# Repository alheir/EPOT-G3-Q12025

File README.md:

# Power Electronics (EPOT) - ITBA
**2025 Q1 - Group 3**

## Members
- Cílfone
- Di Sanzo
- Figueroa
- Gioia
- Heir

## Repository Contents
This repository contains the assignments (TPs) developed for the course 22.14 - Power Electronics of the Electronic Engineering career at ITBA (Instituto Tecnológico de Buenos Aires).

### [TP1: Boost Converter](./tps/tp1/README.md)
Design and simulation of a step-up converter (Boost).

### [TP2: Flyback Converter](./tps/tp2/README.md)
Design and simulation of a Flyback converter, including PCB design.

### [TP3: Inverter](./tps/tp3/README.md)
Implementation of a DC-AC inverter with SPWM generation using ESP32.

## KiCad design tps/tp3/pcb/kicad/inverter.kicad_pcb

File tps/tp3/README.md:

# TP3: Inverter (DC-AC Inverter)

## Description
This assignment consists of implementing a **DC-AC Inverter** using the **SPWM** (Sinusoidal PWM) modulation technique. Signal generation is performed using an **ESP32** microcontroller.

## Features
- **SPWM Generation**: Implemented in firmware for the ESP32.
- **Frequency Control**:
    - **ADC Mode**: Controlled via potentiometer (Pin 34).
    - **Serial Mode**: Commands via terminal to set a specific frequency.
- **Frequency Range**: 15 Hz to 99 Hz.

## Project Structure
- `fw/`: Firmware source code (PlatformIO).
- `pcb/`: Power and control board design.
- `sim/`: Simulations of the power stage and filters.
- `measurements/`: Experimental measurements.
- `assignment/`: Assignment requirements.

## Serial Commands (in `fw`)
- `help`: Shows the command list.
- `mode adc`: Switches to potentiometer control mode.
- `mode serial`: Switches to command control mode.
- `freq <value>`: Sets the frequency (only in serial mode).
- `start`/`stop`: Starts or stops PWM generation.

## PCB Renders
3D Renders of the Inverter control and power board:

> *3D Render - Perspective*:

> *3D Render - Top View*:

> *3D Render - Bottom View*:

## Authors
- G3: Cílfone, Di Sanzo, Figueroa, Gioia, Heir

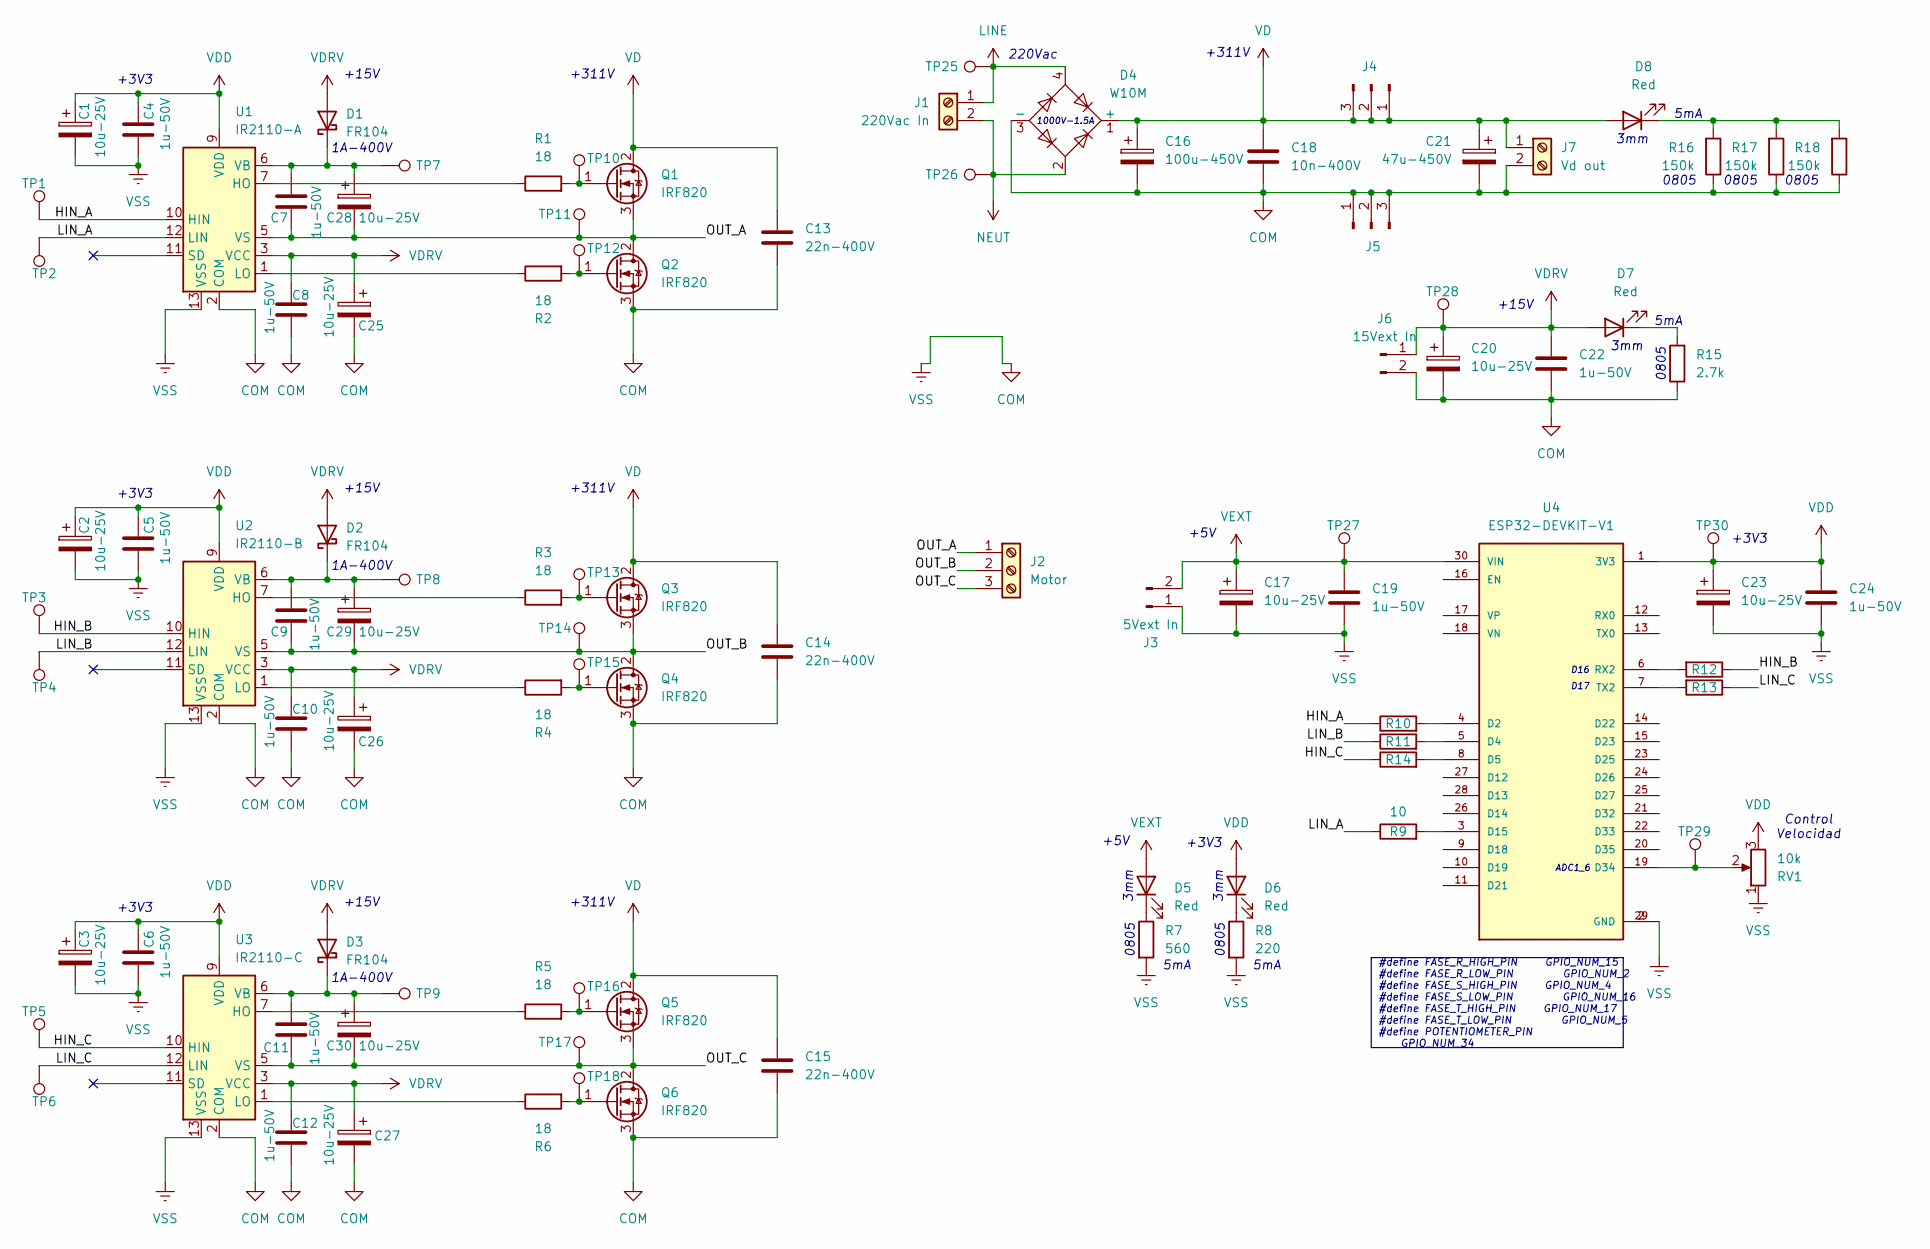
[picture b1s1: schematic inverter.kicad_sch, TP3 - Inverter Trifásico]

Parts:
C1, C2, C3, C17, C20, C23, C25, C26, C27, C28, C29, C30: 10u-25V; CP_Radial_D4.0mm_P1.50mm
C4, C5, C6, C7, C8, C9, C10, C11, C12, C19, C22, C24: 1u-50V; C_Disc_D4.7mm_W2.5mm_P5.00mm
C13, C14, C15: 22n-400V; C_Rect_L11.5mm_W4.0mm_P10.00mm_MKT
C16: 100u-450V; CP_Radial_D17.0mm_P7.50mm
C18: 10n-400V; C_Rect_L11.5mm_W4.5mm_P10.00mm_MKT
C21: 47u-450V; CP_Radial_D16.0mm_P7.50mm
D1, D2, D3: FR104; D_DO-41_SOD81_P10.16mm_Horizontal
D4: W10M; Diode_Bridge_Round_D9.0mm
D5, D6, D7, D8: Red; LED_D3.0mm
J1: 220Vac In; TerminalBlock_bornier-2_P5.08mm
J2: Motor; TerminalBlock_bornier-3_P5.08mm
J3: 5Vext In; Molex_KK-254_AE-6410-02A_1x02_P2.54mm_Vertical
J4, J5: Conn_01x03_Pin; PinHeader_1x03_P2.54mm_Vertical
J6: 15Vext In; Molex_KK-254_AE-6410-02A_1x02_P2.54mm_Vertical
J7: Vd out; TerminalBlock_bornier-2_P5.08mm
Q1, Q2, Q3, Q4, Q5, Q6: IRF820; TO-220-3_Vertical
R1, R2, R3, R4, R5, R6: 18; R_Axial_DIN0204_L3.6mm_D1.6mm_P7.62mm_Horizontal
R7: 560; R_0805_2012Metric_Pad1.20x1.40mm_HandSolder
R8: 220; R_0805_2012Metric_Pad1.20x1.40mm_HandSolder
R9, R10, R11, R12, R13, R14: 10; R_Axial_DIN0207_L6.3mm_D2.5mm_P10.16mm_Horizontal
R15: 2.7k; R_0805_2012Metric_Pad1.20x1.40mm_HandSolder
R16, R17, R18: 150k; R_0805_2012Metric_Pad1.20x1.40mm_HandSolder
RV1: 10k; Potentiometer_Alps_RK163_Single_Horizontal
TP1, TP2, TP3, TP4, TP5, TP6, TP7, TP8, TP9, TP10, TP11, TP12, TP13, TP14, TP15, TP16, TP17, TP18, TP25, TP26, TP27, TP28, TP29, TP30: TestPoint; PinHeader_1x01_P2.54mm_Vertical
U1: IR2110-A; DIP-14_W7.62mm_Socket_LongPads
U2: IR2110-B; DIP-14_W7.62mm_Socket_LongPads
U3: IR2110-C; DIP-14_W7.62mm_Socket_LongPads
U4: ESP32-DEVKIT-V1; MODULE_ESP32_DEVKIT_V1; PARTREV N/A

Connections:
/HIN_A: R10.1, TP1.1, U1.10 (HIN)
/HIN_B: R12.1, TP3.1, U2.10 (HIN)
/HIN_C: R14.1, TP5.1, U3.10 (HIN)
/LIN_A: R9.1, TP2.1, U1.12 (LIN)
/LIN_B: R11.1, TP4.1, U2.12 (LIN)
/LIN_C: R13.1, TP6.1, U3.12 (LIN)
/OUT_A: C7.2, C28.2, J2.1, Q1.3 (S), Q2.2 (D), TP11.1, U1.5 (VS)
/OUT_B: C9.2, C29.2, J2.2, Q3.3 (S), Q4.2 (D), TP14.1, U2.5 (VS)
/OUT_C: C11.2, C30.2, J2.3, Q5.3 (S), Q6.2 (D), TP17.1, U3.5 (VS)
COM: C1.2, C2.2, C3.2, C4.2, C5.2, C6.2, C8.2, C10.2, C12.2, C13.2, C14.2, C15.2, C16.2, C17.2, C18.2, C19.2, C20.2, C21.2, C22.2, C23.2, C24.2, C25.2, C26.2, C27.2, D4.3 (-), J3.1, J5.1, J5.2, J5.3, J6.2, J7.2, Q2.3 (S), Q4.3 (S), Q6.3 (S), R7.2, R8.2, R15.1, R16.1, R17.1, R18.1, RV1.1, U1.2 (COM), U1.13 (VSS), U2.2 (COM), U2.13 (VSS), U3.2 (COM), U3.13 (VSS), U4.2 (GND), U4.29 (GND)
LINE: D4.4, J1.1, TP25.1
NEUT: D4.2, J1.2, TP26.1
unnamed: C7.1, C28.1, D1.1 (K), TP7.1, U1.6 (VB)
unnamed: C9.1, C29.1, D2.1 (K), TP8.1, U2.6 (VB)
unnamed: C11.1, C30.1, D3.1 (K), TP9.1, U3.6 (VB)
unnamed: D5.1 (K), R7.1
unnamed: D6.1 (K), R8.1
unnamed: D7.1 (K), R15.2
unnamed: D8.1 (K), R16.2, R17.2, R18.2
unnamed: Q1.1 (G), R1.2, TP10.1
unnamed: Q2.1 (G), R2.2, TP12.1
unnamed: Q3.1 (G), R3.2, TP13.1
unnamed: Q4.1 (G), R4.2, TP15.1
unnamed: Q5.1 (G), R5.2, TP16.1
unnamed: Q6.1 (G), R6.2, TP18.1
unnamed: R1.1, U1.7 (HO)
unnamed: R2.1, U1.1 (LO)
unnamed: R3.1, U2.7 (HO)
unnamed: R4.1, U2.1 (LO)
unnamed: R5.1, U3.7 (HO)
unnamed: R6.1, U3.1 (LO)
unnamed: R10.2, U4.4 (D2)
unnamed: R11.2, U4.5 (D4)
unnamed: R14.2, U4.8 (D5)
unnamed: R9.2, U4.3 (D15)
unnamed: RV1.2, TP29.1, U4.19 (D34)
unnamed: R12.2, U4.6 (RX2)
unnamed: R13.2, U4.7 (TX2)
VD: C13.1, C14.1, C15.1, C16.1, C18.1, C21.1, D4.1 (+), D8.2 (A), J4.1, J4.2, J4.3, J7.1, Q1.2 (D), Q3.2 (D), Q5.2 (D)
VDD: C1.1, C2.1, C3.1, C4.1, C5.1, C6.1, C23.1, C24.1, D6.2 (A), RV1.3, TP30.1, U1.9 (VDD), U2.9 (VDD), U3.9 (VDD), U4.1 (3V3)
VDRV: C8.1, C10.1, C12.1, C20.1, C22.1, C25.1, C26.1, C27.1, D1.2 (A), D2.2 (A), D3.2 (A), D7.2 (A), J6.1, TP28.1, U1.3 (VCC), U2.3 (VCC), U3.3 (VCC)
VEXT: C17.1, C19.1, D5.2 (A), J3.2, TP27.1, U4.30 (VIN)

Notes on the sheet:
0805
5mA
+3V3
Control Velocidad
3mm
+311V
+15V
+5V
1A-400V
220Vac
D17
1000V-1.5A
ADC1_6
D16
#define FASE_R_HIGH_PIN GPIO_NUM_15 #define FASE_R_LOW_PIN GPIO_NUM_2 #define FASE_S_HIGH_PIN GPIO_NUM_4 #define FASE_S_LOW_PIN GPIO_NUM_16 #define FASE_T_HIGH_PIN GPIO_NUM_17 #define FASE_T_LOW_PIN GPIO_NUM_5 #define POTENTIOMETER_PIN GPIO_NUM_34

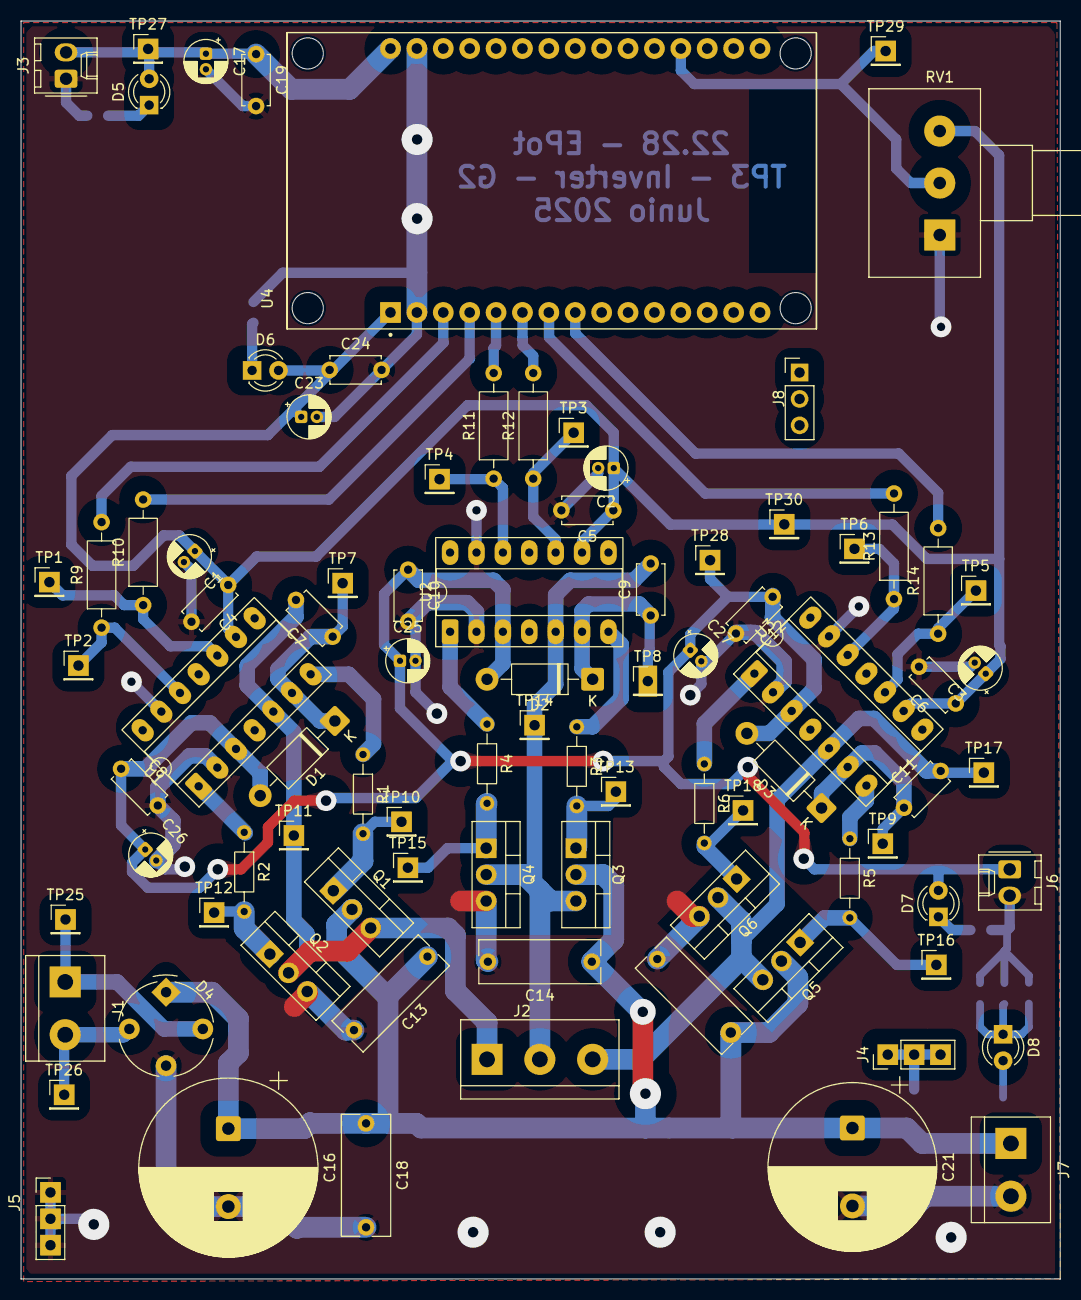
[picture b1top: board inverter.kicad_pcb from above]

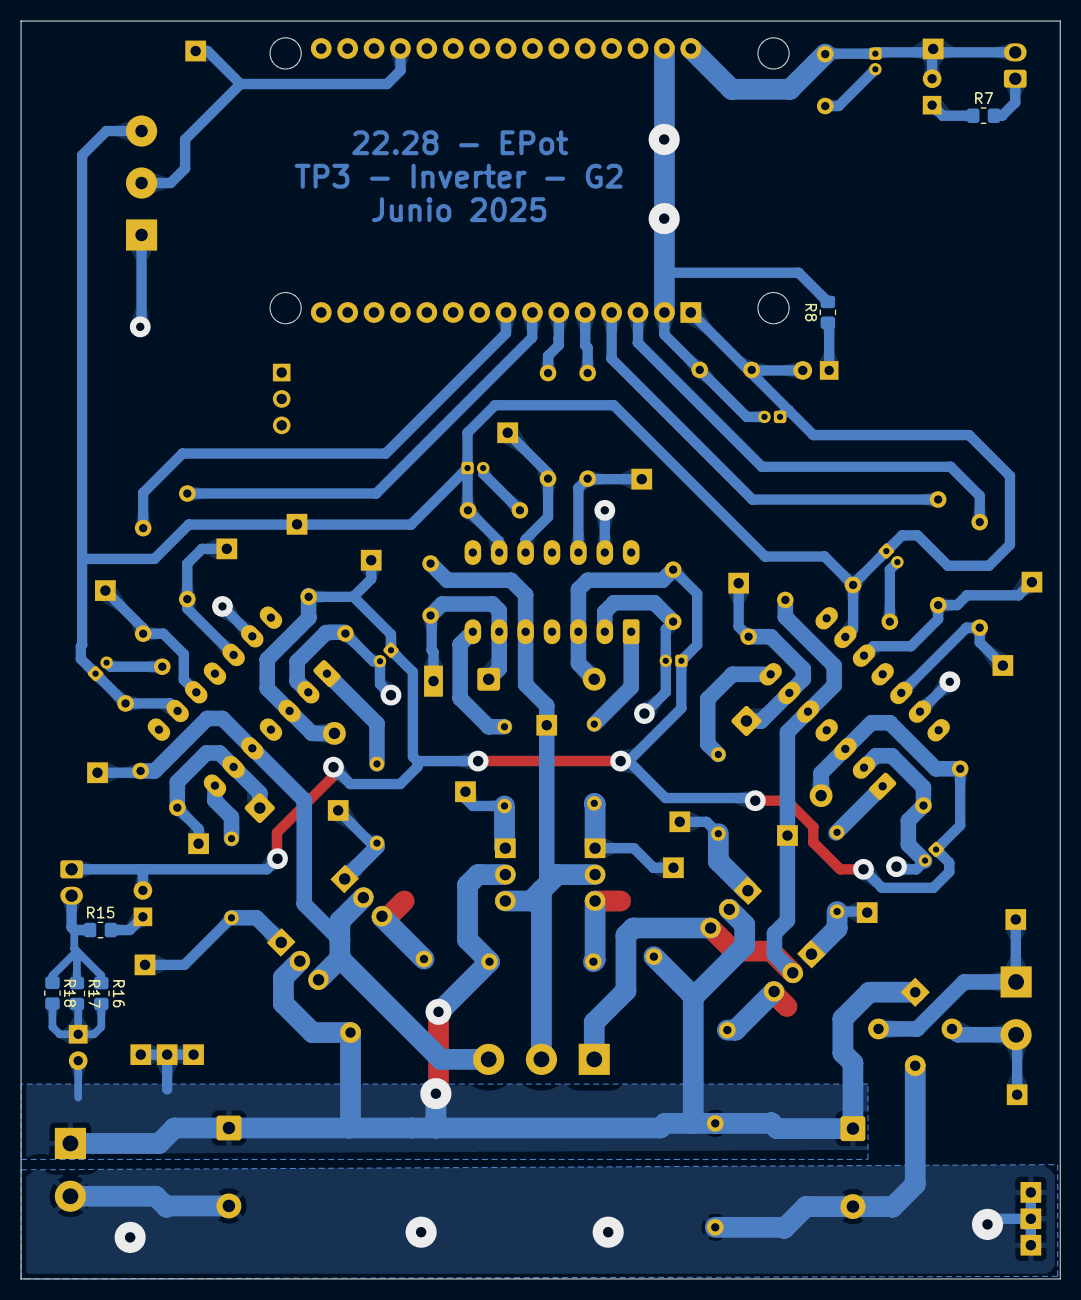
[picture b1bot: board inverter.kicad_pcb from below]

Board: 2 copper layers, 100.0 x 121.0 mm, 94 parts (6 on the bottom side), 42 nets.

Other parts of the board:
J8: Conn_01x03_Pin; PinHeader_1x03_P2.54mm_Vertical

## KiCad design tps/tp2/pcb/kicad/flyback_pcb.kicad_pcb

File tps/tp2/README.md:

# TP2: Flyback Converter

## Description
This assignment covers the design, simulation, and PCB layout of a **Flyback** DC-DC converter topology.

## Project Structure
- `sim/`: Circuit simulations.
- `pcb/`: Printed Circuit Board design.
- `Datasheets/`: Data sheets for critical components.
- `assignment/`: Assignment requirements.
- `plots/`: Plots of obtained results.
- `entrega/`: Final documentation presented.

## Hardware and PCB
Representative images of the PCB design and the final hardware:

> *3D Render - Front*:

> *3D Render - Back*:

> *PCB Routing*:

> *Assembled Flyback Converter*:

## Authors
- G3: Cílfone, Di Sanzo, Figueroa, Gioia, Heir

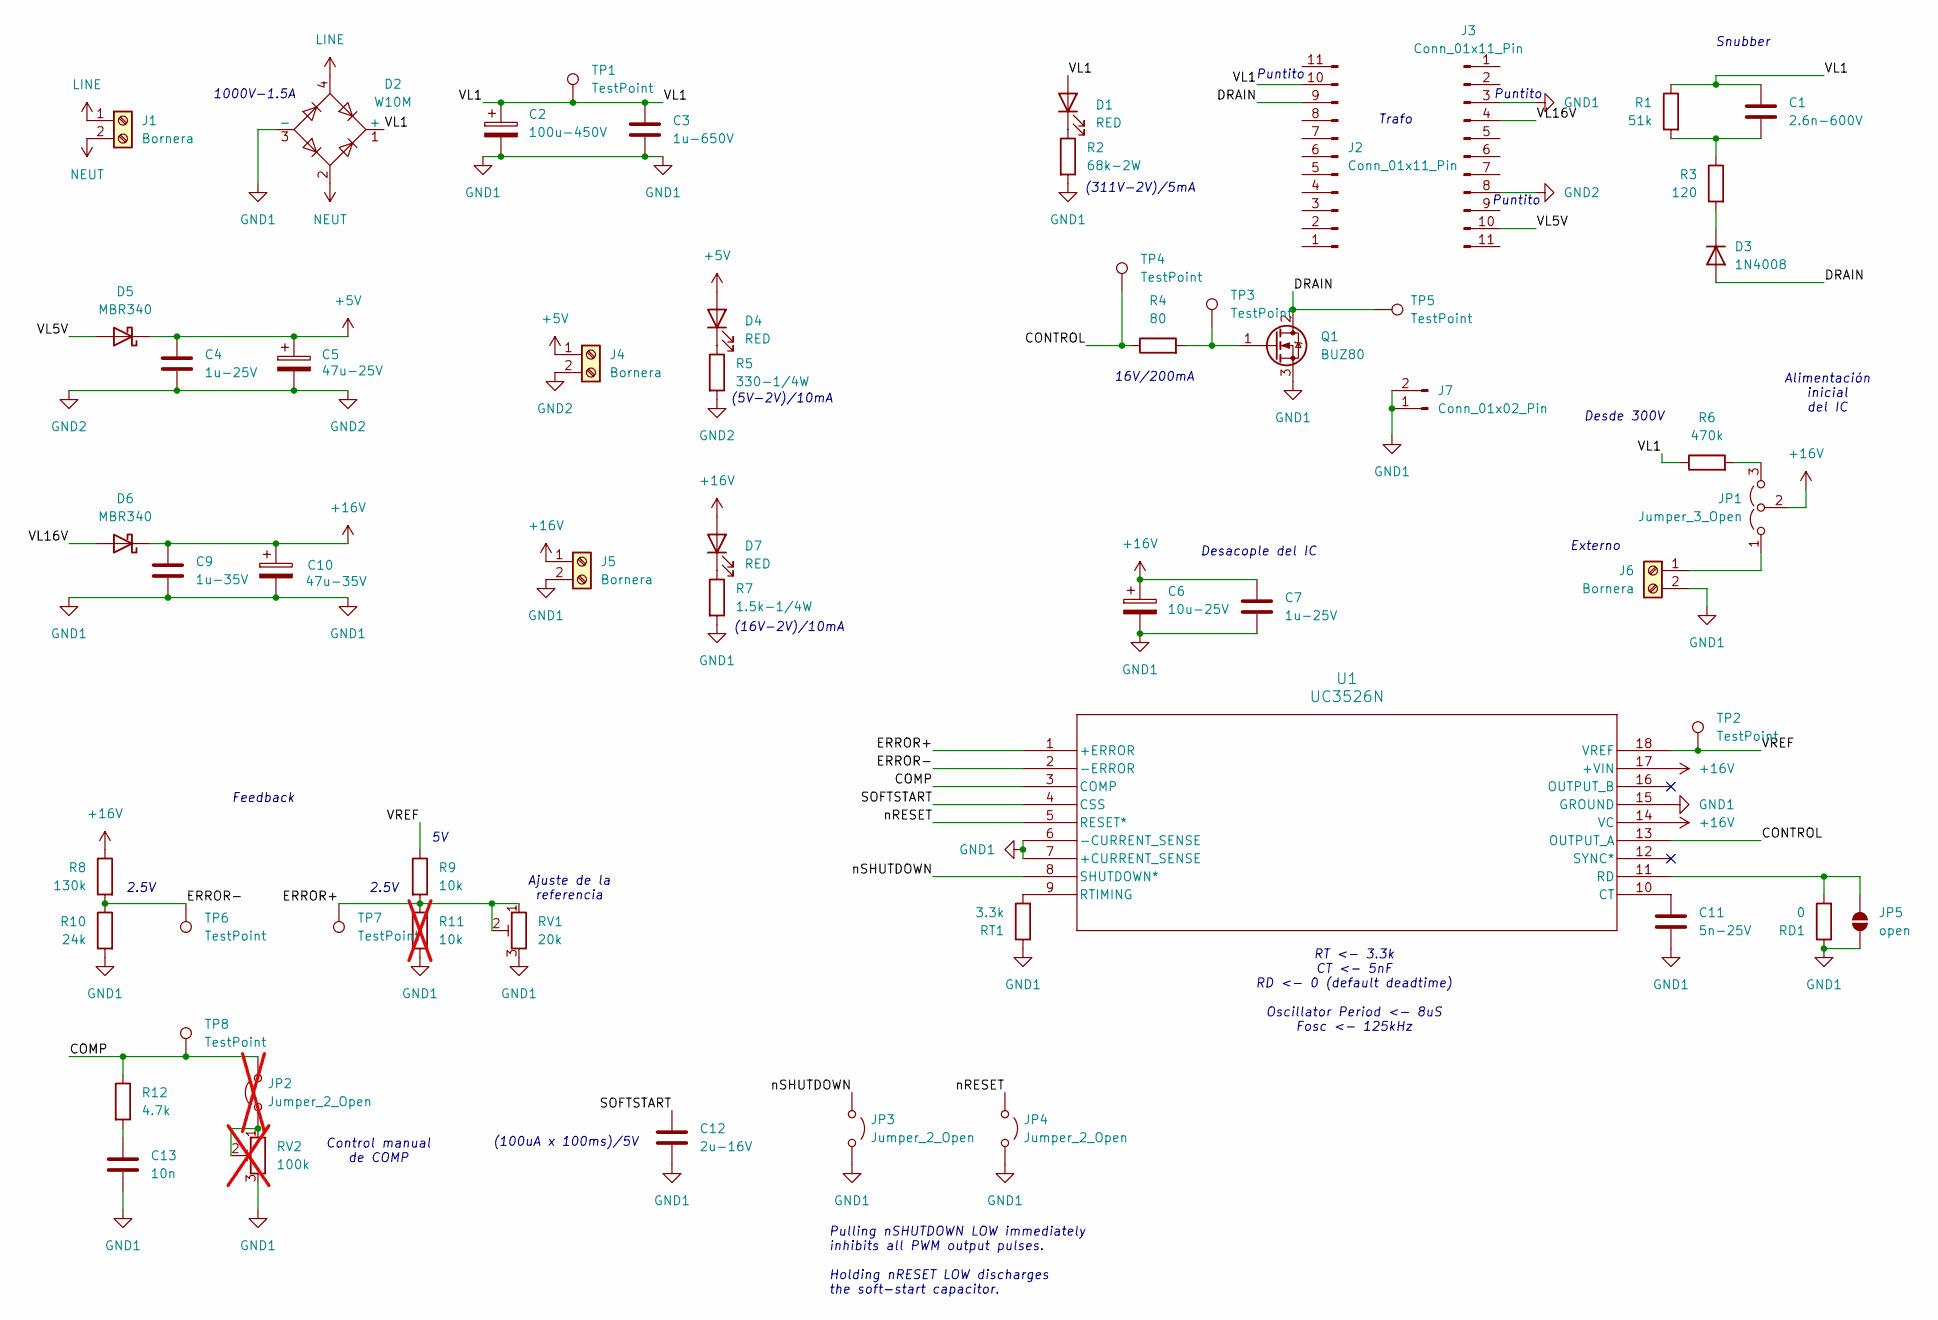
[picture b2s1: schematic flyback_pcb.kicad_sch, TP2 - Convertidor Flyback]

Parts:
C1: 2.6n-600V; C_Disc_D4.3mm_W1.9mm_P5.00mm
C2: 100u-450V; CP_Radial_D17.0mm_P7.50mm
C3: 1u-650V; C_Rect_L27.0mm_W9.0mm_P22.00mm
C4, C7: 1u-25V; C_Disc_D4.3mm_W1.9mm_P5.00mm
C5: 47u-25V; CP_Radial_D7.5mm_P2.50mm
C6: 10u-25V; CP_Radial_D7.5mm_P2.50mm
C9: 1u-35V; C_Disc_D4.3mm_W1.9mm_P5.00mm
C10: 47u-35V; CP_Radial_D7.5mm_P2.50mm
C11: 5n-25V; C_Disc_D4.3mm_W1.9mm_P5.00mm
C12: 2u-16V; C_Disc_D4.3mm_W1.9mm_P5.00mm
C13: 10n; C_Disc_D4.3mm_W1.9mm_P5.00mm
D1, D4, D7: RED; LED_D3.0mm
D2: W10M; Diode_Bridge_Round_D9.0mm
D3: 1N4008; D_DO-41_SOD81_P10.16mm_Horizontal
D5, D6: MBR340; D_DO-201AD_P15.24mm_Horizontal
J1, J4, J5, J6: Bornera; TerminalBlock_bornier-2_P5.08mm
J2, J3: Conn_01x11_Pin; PhoenixContact_MSTB_2,5_11-GF_1x11_P5.00mm_Horizontal_Threa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
J7: Conn_01x02_Pin; PinHeader_1x02_P2.54mm_Vertical
JP1: Jumper_3_Open; PinHeader_1x03_P2.54mm_Vertical
JP2: Jumper_2_Open; TestPoint_2Pads_Pitch2.54mm_Drill0.8mm; not fitted
JP3, JP4: Jumper_2_Open; PinHeader_1x02_P2.54mm_Vertical
JP5: open; SolderJumper-2_P1.3mm_Open_Pad1.0x1.5mm
Q1: BUZ80; TO-220-3_Vertical
R1: 51k; R_Axial_DIN0207_L6.3mm_D2.5mm_P7.62mm_Horizontal
R2: 68k-2W; R_Axial_DIN0207_L6.3mm_D2.5mm_P7.62mm_Horizontal
R3: 120; R_Axial_DIN0207_L6.3mm_D2.5mm_P7.62mm_Horizontal
R4: 80; R_Axial_DIN0207_L6.3mm_D2.5mm_P7.62mm_Horizontal
R5: 330-1/4W; R_0805_2012Metric_Pad1.20x1.40mm_HandSolder
R6: 470k; R_Axial_DIN0207_L6.3mm_D2.5mm_P7.62mm_Horizontal
R7: 1.5k-1/4W; R_0805_2012Metric_Pad1.20x1.40mm_HandSolder
R8: 130k; R_Axial_DIN0207_L6.3mm_D2.5mm_P7.62mm_Horizontal
R9: 10k; R_Axial_DIN0207_L6.3mm_D2.5mm_P7.62mm_Horizontal
R10: 24k; R_Axial_DIN0207_L6.3mm_D2.5mm_P7.62mm_Horizontal
R11: 10k; R_Axial_DIN0207_L6.3mm_D2.5mm_P7.62mm_Horizontal; not fitted
R12: 4.7k; R_Axial_DIN0207_L6.3mm_D2.5mm_P7.62mm_Horizontal
RD1: 0; R_Axial_DIN0207_L6.3mm_D2.5mm_P7.62mm_Horizontal
RT1: 3.3k; R_Axial_DIN0207_L6.3mm_D2.5mm_P7.62mm_Horizontal
RV1: 20k; Potentiometer_Bourns_3266Y_Vertical
RV2: 100k; Potentiometer_Bourns_3266Y_Vertical; not fitted
TP1, TP2, TP3, TP4, TP5, TP6, TP7, TP8: TestPoint; Pin_D1.0mm_L10.0mm
U1: UC3526N; N18

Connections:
+5V: C4.1, C5.1, D4.2 (A), D5.1 (K), J4.1
+16V: C6.1, C7.1, C9.1, C10.1, D6.1 (K), D7.2 (A), J5.1, JP1.2 (C), R8.1, U1.14 (VC), U1.17 (+VIN)
/COMP: JP2.2 (B), R12.1, TP8.1, U1.3 (COMP)
/CONTROL: R4.1, TP4.1, U1.13 (OUTPUT_A)
/DRAIN: D3.2 (A), J2.9, Q1.2 (D), TP5.1
/ERROR+: R9.2, R11.1, RV1.1, RV1.2, TP7.1, U1.1 (+ERROR)
/ERROR-: R8.2, R10.1, TP6.1, U1.2 (-ERROR)
/SOFTSTART: C12.1, U1.4 (CSS)
/VL1: C1.1, C2.1, C3.1, D1.2 (A), D2.1 (+), J2.10, R1.1, R6.1, TP1.1
/VL5V: D5.2 (A), J3.10
/VL16V: D6.2 (A), J3.4
/VREF: R9.1, TP2.1, U1.18 (VREF)
/nRESET: JP4.1 (A), U1.5 (RESET*)
/nSHUTDOWN: JP3.1 (A), U1.8 (SHUTDOWN*)
GND1: C2.2, C3.2, C6.2, C7.2, C9.2, C10.2, C11.2, C12.2, C13.2, D2.3 (-), J3.3, J5.2, J6.2, J7.1, J7.2, JP3.2 (B), JP4.2 (B), JP5.1 (A), Q1.3 (S), R2.2, R7.2, R10.2, R11.2, RD1.1, RT1.1, RV1.3, RV2.3, U1.6 (-CURRENT_SENSE), U1.7 (+CURRENT_SENSE), U1.15 (GROUND)
GND2: C4.2, C5.2, J3.8, J4.2, R5.2
LINE: D2.4, J1.1
NEUT: D2.2, J1.2
unnamed: C1.2, R1.2, R3.1
unnamed: C13.1, R12.2
unnamed: D1.1 (K), R2.1
unnamed: D3.1 (K), R3.2
unnamed: D4.1 (K), R5.1
unnamed: D7.1 (K), R7.1
unnamed: J6.1, JP1.1 (A)
unnamed: JP1.3 (B), R6.2
unnamed: JP2.1 (A), RV2.1, RV2.2
unnamed: JP5.2 (B), RD1.2, U1.11 (RD)
unnamed: Q1.1 (G), R4.2, TP3.1
unnamed: C11.1, U1.10 (CT)
unnamed: RT1.2, U1.9 (RTIMING)

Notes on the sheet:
Pulling nSHUTDOWN LOW immediately inhibits all PWM output pulses. Holding nRESET LOW discharges the soft-start capacitor.
16V/200mA
Snubber
Feedback
2.5V
Trafo
Desde 300V
(5V-2V)/10mA
Desacople del IC
Control manual de COMP
Ajuste de la referencia
Alimentación inicial del IC
Externo
RT <- 3.3k CT <- 5nF RD <- 0 (default deadtime) Oscillator Period <- 8uS Fosc <- 125kHz
(100uA x 100ms)/5V
1000V-1.5A
(311V-2V)/5mA
Puntito
(16V-2V)/10mA

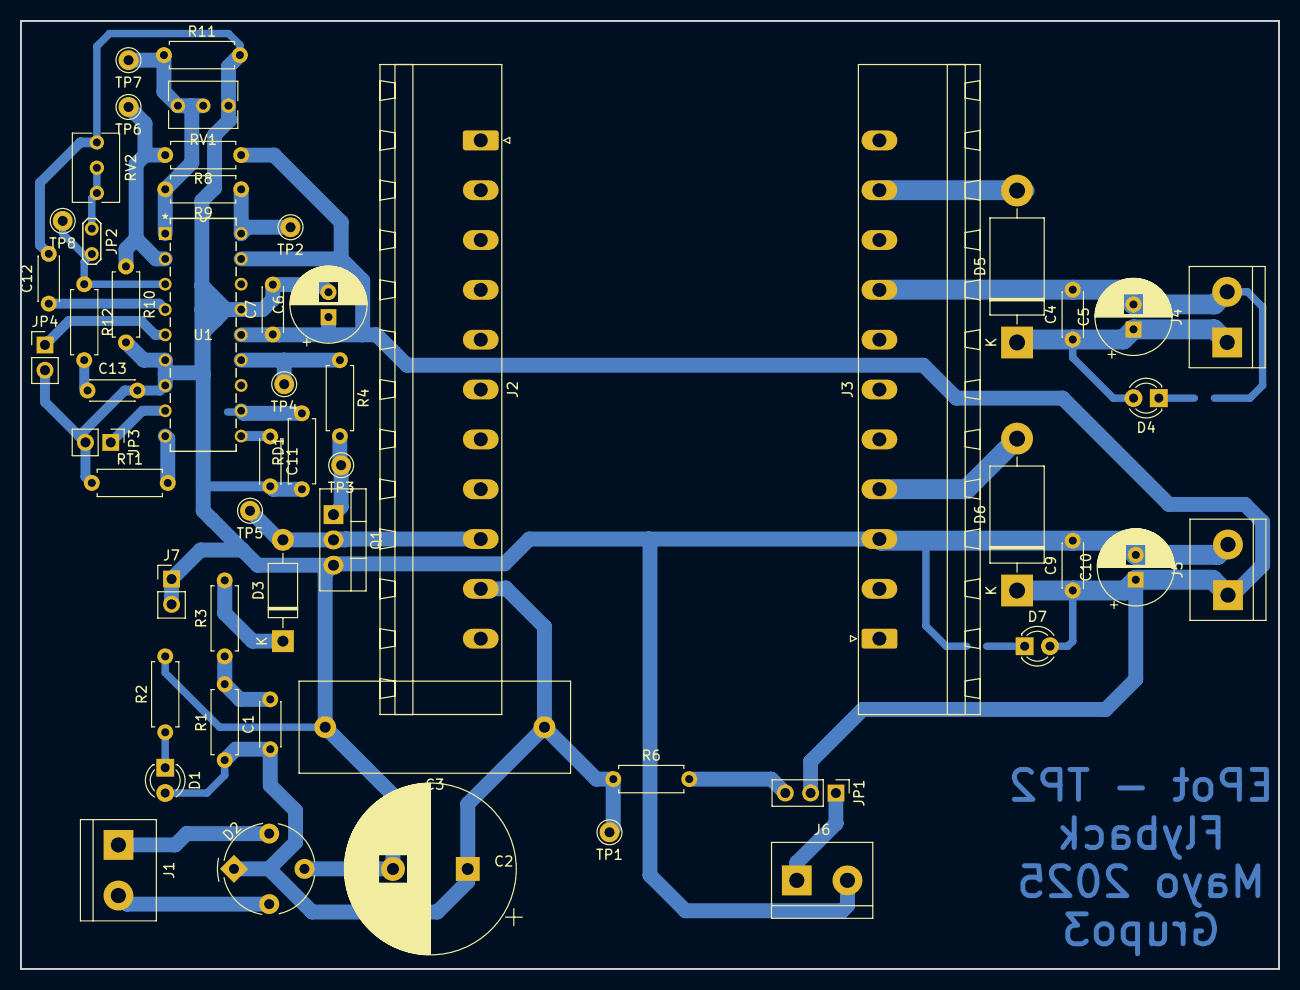
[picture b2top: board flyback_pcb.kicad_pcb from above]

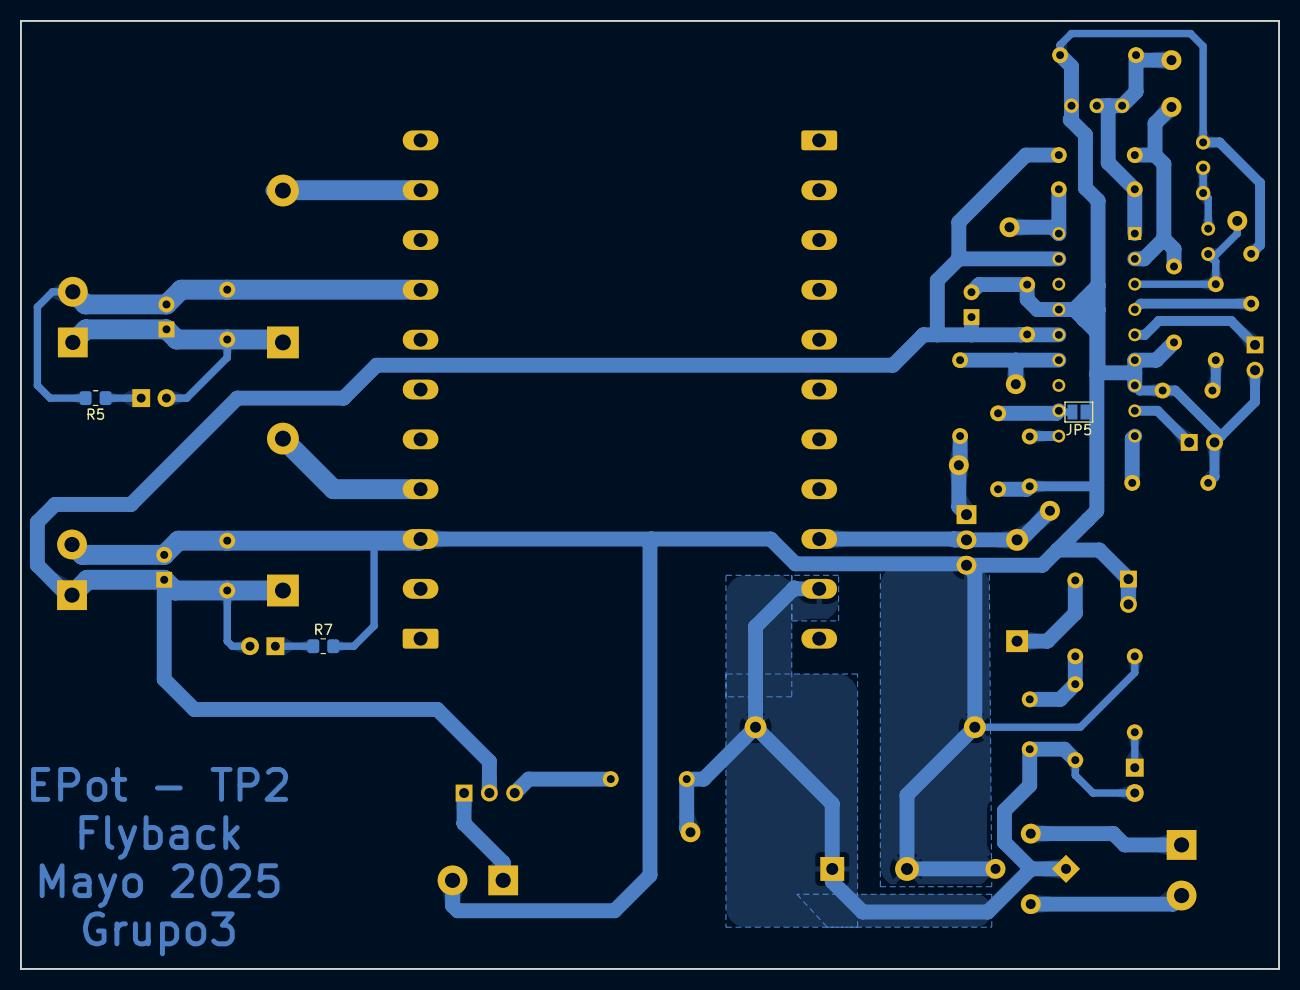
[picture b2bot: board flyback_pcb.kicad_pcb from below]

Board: 2 copper layers, 126.2 x 95.1 mm, 57 parts (3 on the bottom side), 31 nets.

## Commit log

2025-03-23 Add LTspice gitignore and initial full_ideal simulation file for tp1
2025-03-23 real
2025-03-23 Ya entendimos lo basico
2025-03-23 Circuito completo Boost
2025-03-23 Boost completa + ojo con la inversion de la señal de switching
2025-03-24 Un par de resistencias
2025-04-04 spice update
2025-04-06 falta ver la oscilación de Vds
2025-04-06 Circuito final
2025-04-07 imagenes y simulacion final tp1
2025-05-04 plots y entrega tp1
2025-05-04 Add TP2 Flyback assignment
2025-05-04 Add LTspice simulation files and .gitignore for TP2
2025-05-04 Add custom comparator and PWM controller models for TP2 simulation
2025-05-10 Agrego avances PCB Flyback (KiCad)
2025-05-10 avances sch flyback + sch en pdf
2025-05-10 fix nodo alimentación bornera J6
2025-05-10 agrego diodo en serie a la alimentación externa del IC
2025-05-14 add cap footprints
2025-05-14 add missing footprints
2025-05-14 fix transformer pin assignments
2025-05-14 transformer pcb layout
2025-05-14 routeado sin circuito de switching (UC3526)
2025-05-14 1era versión pcb a fabricar
2025-05-16 add routing and 3D views; update footprint dimensions for capacitors
2025-05-28 add current loops image and update flyback PCB schematic with final components values
2025-05-28 update tp2 pdf sch
2025-05-28 flyback
2025-05-30 Hay que ver como manejar colisiones de Rd y (rs1 o rs2)
2025-05-31 add raw measurements of flyback
2025-05-31 add measurements plots for flyback
2025-05-31 update flyback schematic with component value changes and add new PDF files for schematics
2025-05-31 add final report for flyback
2025-06-01 add initial inverter (TP3) schematic (kicad)
2025-06-01 refactor inverter sch: replace VIC labels with VDRV labels
2025-06-06 add .gitignore files for LTspice and MATLAB simulations
2025-06-06 add initial PlatformIO project structure for ESP32 fw
2025-06-06 inverter sch visual improvements
2025-06-06 add TP3 assignment
2025-06-06 Add Vd out
2025-06-07 ver de debuggear esto
2025-06-07 fix inverter sch after feedback and real component sizes, start PCB routing
2025-06-07 Add WIP inverter spice (ideal)
2025-06-07 version con potenciometro y ma, mf, v-f constante
    como te vas a olvidar la digi ameo
2025-06-07 add more 15V decoupling caps, update exported sch, add potentiometer 3D model, some routing progress
2025-06-09 Avances en SPWM
2025-06-11 working
2025-06-12 version final pwm
2025-06-12 add base matlab inverter sim
2025-06-13 push 4 ale
2025-06-13 int casts
2025-06-13 avances pcb
2025-06-13 fix duty variable
2025-06-13 timer f to 10M, group f to 100M
2025-06-13 fix deadtime
2025-06-13 serial menu, 1st try
2025-06-13 pcb aprobado por Victor y Pablo
2025-06-13 routeo (en proceso) aprobado por Victor y Pablo
2025-06-26 Add new measurement and PCB images for documentation
2025-06-27 final inverter pcb
2025-06-27 Add LED activity indication and frequency reporting in setup and loop
2026-02-12 feat: Add detailed READMEs for TP1, TP2, and TP3, and update the main project README with an overview and links.
2026-02-12 chore: Remove unnecessary .DS_Store files and add to .gitignore
